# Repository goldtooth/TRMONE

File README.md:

View this project on [CADLAB.io](https://cadlab.io/project/1551). 

# TREMONE

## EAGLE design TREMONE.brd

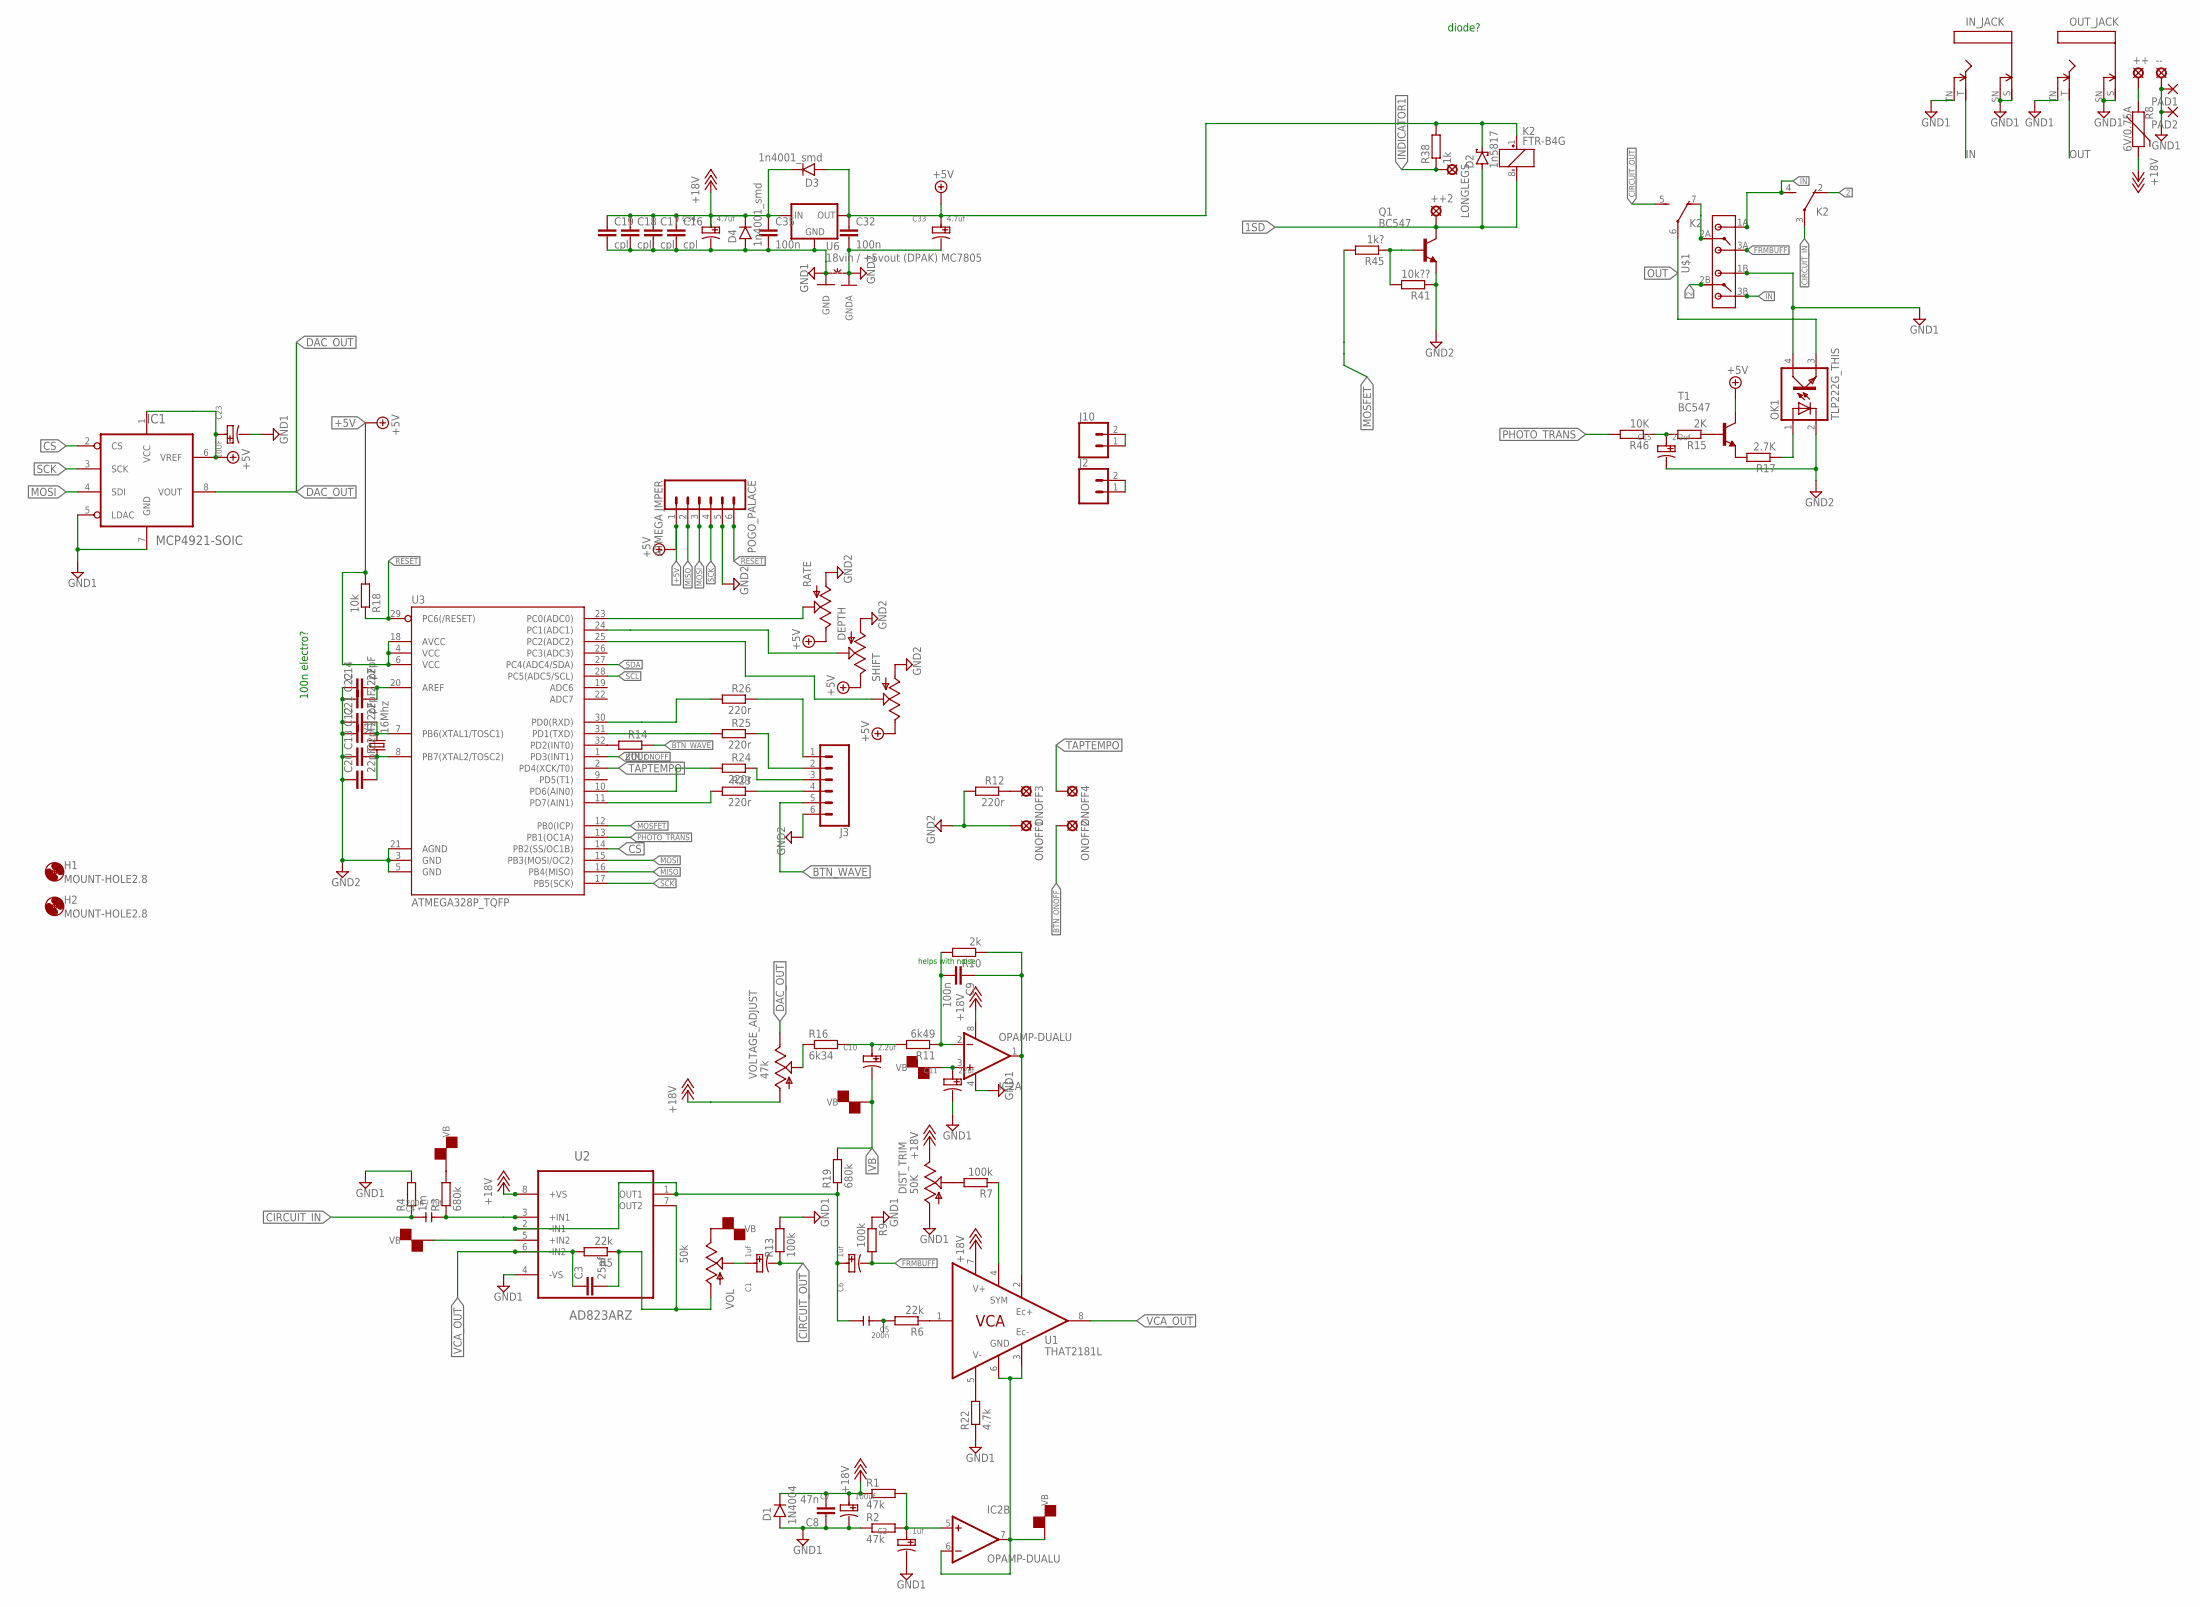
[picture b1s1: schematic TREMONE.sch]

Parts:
++, ++2: LSP10
--: LSP10
C1, C2, C6: 1uf; PC-D5.3MM
C3: 25pf; C1206
C4: 200n / 1uf; CERAMIC-5MM
C5: 200n; CERAMIC-5MM
C7: 100uf; PC-D5.3MM
C8: 47n; C1206
C9, C32, C35: 100n; C1206
C10, C15: 2.2uf; PC-D5.3MM
C11: 22uf; PC-D5.3MM
C12, C13, C22: 22pF; 0603
C14, C20, C21: 22pF; CAP-PTH-2.54
C16, C17, C18, C19: cpl; C1206
C23: 10UF; PC-D5.3MM
C33, C34: 4.7uf; PC-D5.3MM
D1: 1N4004; DO41-1
D2: 1n5817; SMB
D3, D4: 1n4001_smd; DO41-1
DEPTH: POT; ALPS_POT
DIST_TRIM: 50K; 3223G
H1, H2: MOUNT-HOLE2.8; 2,8
IC1: MCP4921-SOIC; SOIC-8
IC2: OPAMP-DUALU; SO08
IN_JACK: MMMONNNNOHOLES; MONONOHOLES
J2, J10: CONN_02PTH3; 1X02_LONGPADS
J3: CONN_06NO_SILK_FEMALE_PTH; 1X06_NO_SILK
K2: FTR-B4G
LONGLEGS: LSP10
OK1: TLP222G_THIS; DIL04
ONOFF1, ONOFF2, ONOFF3, ONOFF4: LSP10
OUT_JACK: MMMONNNNOHOLES; MONONOHOLES
PAD1, PAD2: SMD5; SMD2,54-5,08
POGO_PALACE: ATMEGA JMPER; 1X06_LONGPADS
Q1: BC547; TO92
R1, R2: 47k; M1206
R3, R19: 680k; M1206
R4: 1m; M1206
R5, R6: 22k; M1206
R7, R9, R13: 100k; M1206
R8: 6V/0.75A; 1206
R10: 2k; M1206
R11: 6k49; M1206
R12, R23, R24, R25, R26: 220r; M1206
R14: 200r; M1206
R15: 2K; M1206
R16: 6k34; M1206
R17: 2.7K; M1206
R18: 10k; M1206
R22: 4.7k; M1206
R38: 1k; M1206
R41: 10k??; M1206
R45: 1k?; M1206
R46: 10K; M1206
RATE: POT; ALPS_POT
SHIFT: POT; ALPS_POT
T1: BC547; TO92
U1: THAT2181L; SIP8
U2: AD823ARZ; SOIC127P600X175-8N
U3: ATMEGA328P_TQFP; TQFP32-08
U6: 18vin / +5vout (DPAK) MC7805; TO-252
U$1: BYSWITCH; BUFF/TRBYPASS
VOL: 50k; ALPS_POT
VOLTAGE_ADJUST: 47k; 3223G
Y1: 16Mhz; HC49US
~NUDEV~1: GND-GNDA1,27MM; GND-GNDA-1,27MM

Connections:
1SD: ++2.MP, D2.A, K2.8 (-), Q1.3 (C)
2: K2.2 (O), U$1.2B
+5V: C23.+, C32.1, C33.+, D2.C, D3.A, DEPTH.P$1 (E), IC1.1 (VCC), IC1.6 (VREF), K2.1 (+), POGO_PALACE.1, R18.2, R38.2, RATE.P$1 (E), SHIFT.P$1 (E), T1.3 (C), U3.4 (VCC), U3.6 (VCC), U3.18 (AVCC), U6.2 (OUT)
+18V: C7.+, C8.2, C16.1, C17.1, C18.1, C19.1, C34.+, C35.1, D1.C, D3.C, D4.C, DIST_TRIM.3 (E), IC2.8 (V+), R1.1, R8.2, U1.7 (V+), U2.8 (+VS), U6.1 (IN), VOLTAGE_ADJUST.1 (A)
BTN_ONOFF: ONOFF2.MP, U3.1 (PD3(INT1))
BTN_WAVE: J3.5, R14.1
CIRCUIT_IN: C4.1, K2.3, R4.1
CIRCUIT_OUT: C1.-, K2.5 (S), R13.1
CS: IC1.2 (CS), U3.14 (PB2(SS/OC1B))
DAC_OUT: IC1.8 (VOUT), VOLTAGE_ADJUST.3 (E)
FRMBUFF: C6.-, R9.2, U$1.3A
GND1: --.MP, C2.-, C7.-, C8.1, C11.-, C16.2, C17.2, C18.2, C19.2, C23.-, C34.-, C35.2, D1.A, D4.A, DIST_TRIM.1 (A), IC1.5 (LDAC), IC1.7 (GND), IC2.4 (V-), IN_JACK.S, IN_JACK.SN, IN_JACK.TN, OK1.4 (COL), OUT_JACK.S, OUT_JACK.SN, OUT_JACK.TN, PAD1.1, PAD2.1, R2.1, R4.2, R9.1, R13.2, R22.1, U2.4 (-VS), U6.3 (GND), U$1.1B, ~NUDEV~1.GND
GND2: C12.1, C13.1, C14.1, C15.-, C20.1, C21.1, C22.1, C32.2, C33.-, DEPTH.P$3 (A), J3.6, OK1.2 (C), ONOFF1.MP, POGO_PALACE.5, Q1.1 (E), R12.2, R41.1, RATE.P$3 (A), SHIFT.P$3 (A), U3.3 (GND), U3.5 (GND), U3.21 (AGND), ~NUDEV~1.GNDA
IN: IN_JACK.T, K2.4 (S), U$1.1A, U$1.3B
INDICATOR1: LONGLEGS.MP, R38.1
MISO: POGO_PALACE.2, U3.16 (PB4(MISO))
MOSFET: R45.2, U3.12 (PB0(ICP))
MOSI: IC1.4 (SDI), POGO_PALACE.3, U3.15 (PB3(MOSI/OC2))
unnamed: C4.2, R3.1, U2.3 (+IN1)
unnamed: C2.+, IC2.5 (+IN), R1.2, R2.2
unnamed: ONOFF3.MP, R12.1
unnamed: R16.1, VOLTAGE_ADJUST.2 (S)
unnamed: C3.2, R5.1, U2.7 (OUT2), VOL.P$3 (A)
unnamed: C5.2, C6.+, R19.1, U2.1 (OUT1), U2.2 (-IN1)
unnamed: C5.1, R6.2
unnamed: R6.1, U1.1 (IN)
unnamed: C1.+, VOL.P$2 (S)
unnamed: J2.1, J2.2
unnamed: R7.1, U1.4 (SYM)
unnamed: DIST_TRIM.2 (S), R7.2
unnamed: C13.2, C20.2, U3.8 (PB7(XTAL2/TOSC2)), Y1.1
unnamed: C9.2, IC2.2 (-IN), R10.2, R11.1
unnamed: C12.2, C21.2, U3.7 (PB6(XTAL1/TOSC1)), Y1.2
unnamed: C14.2, C22.2, U3.20 (AREF)
unnamed: J3.4, R23.1
unnamed: J3.3, R24.1
unnamed: J3.2, R25.1
unnamed: J10.1, J10.2
unnamed: R22.2, U1.5 (V-)
unnamed: J3.1, R26.1
unnamed: R26.2, U3.30 (PD0(RXD))
unnamed: R25.2, U3.31 (PD1(TXD))
unnamed: R24.2, U3.10 (PD6(AIN0))
unnamed: R23.2, U3.11 (PD7(AIN1))
unnamed: RATE.P$2 (S), U3.23 (PC0(ADC0))
unnamed: DEPTH.P$2 (S), U3.24 (PC1(ADC1))
unnamed: SHIFT.P$2 (S), U3.25 (PC2(ADC2))
unnamed: R14.2, U3.32 (PD2(INT0))
unnamed: C15.+, R15.2, R46.1
unnamed: R15.1, T1.2 (B)
unnamed: ++.MP, R8.1
unnamed: C9.1, IC2.1 (OUT), R10.1, U1.2 (EC+)
unnamed: R17.2, T1.1 (E)
unnamed: OK1.1 (A), R17.1
unnamed: K2.7 (O), U$1.2A
unnamed: Q1.2 (B), R41.2, R45.1
OUT: K2.6, OK1.3 (EMIT), OUT_JACK.T
PHOTO_TRANS: R46.2, U3.13 (PB1(OC1A))
R: C10.+, R11.2, R16.2
RESET: POGO_PALACE.6, R18.1, U3.29 (PC6(/RESET))
SCK: IC1.3 (SCK), POGO_PALACE.4, U3.17 (PB5(SCK))
SCL: U3.28 (PC5(ADC5/SCL))
SDA: U3.27 (PC4(ADC4/SDA))
TAPTEMPO: ONOFF4.MP, U3.2 (PD4(XCK/T0))
VB: C10.-, C11.+, IC2.3 (+IN), IC2.6 (-IN), IC2.7 (OUT), R3.2, R19.2, U1.3 (EC-), U1.6 (GND), U2.5 (+IN2), VOL.P$1 (E)
VCA_OUT: C3.1, R5.2, U1.8 (OUT), U2.6 (-IN2)

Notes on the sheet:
100n electro?
helps with noise
diode?

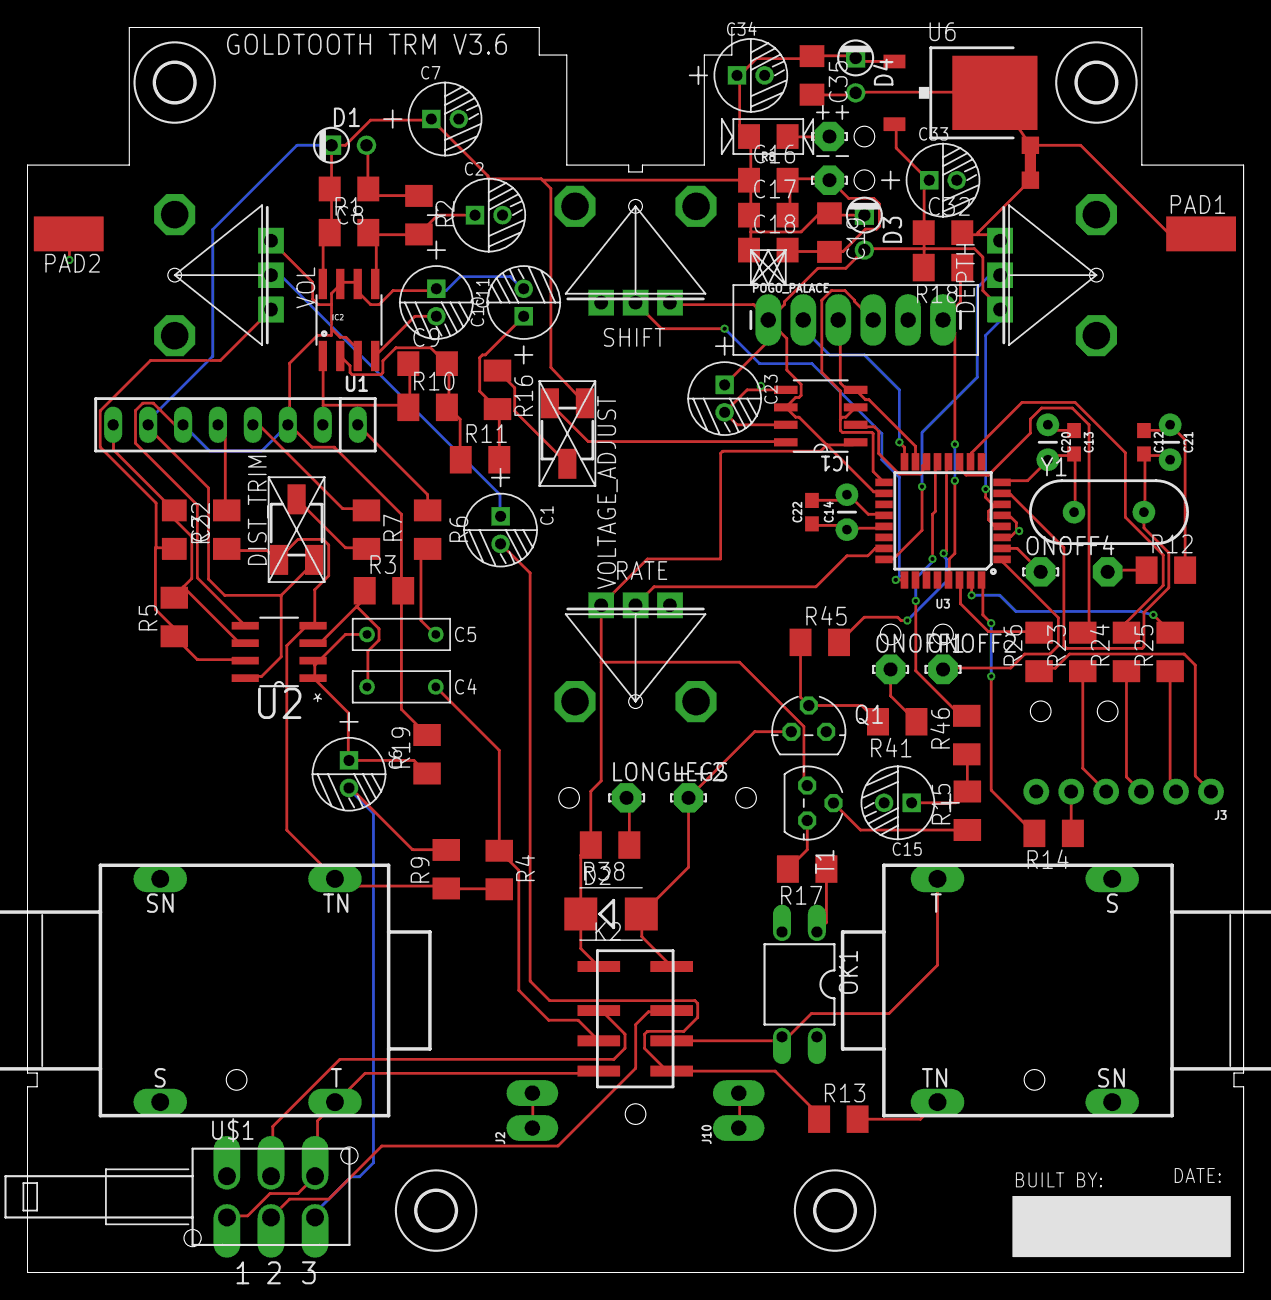
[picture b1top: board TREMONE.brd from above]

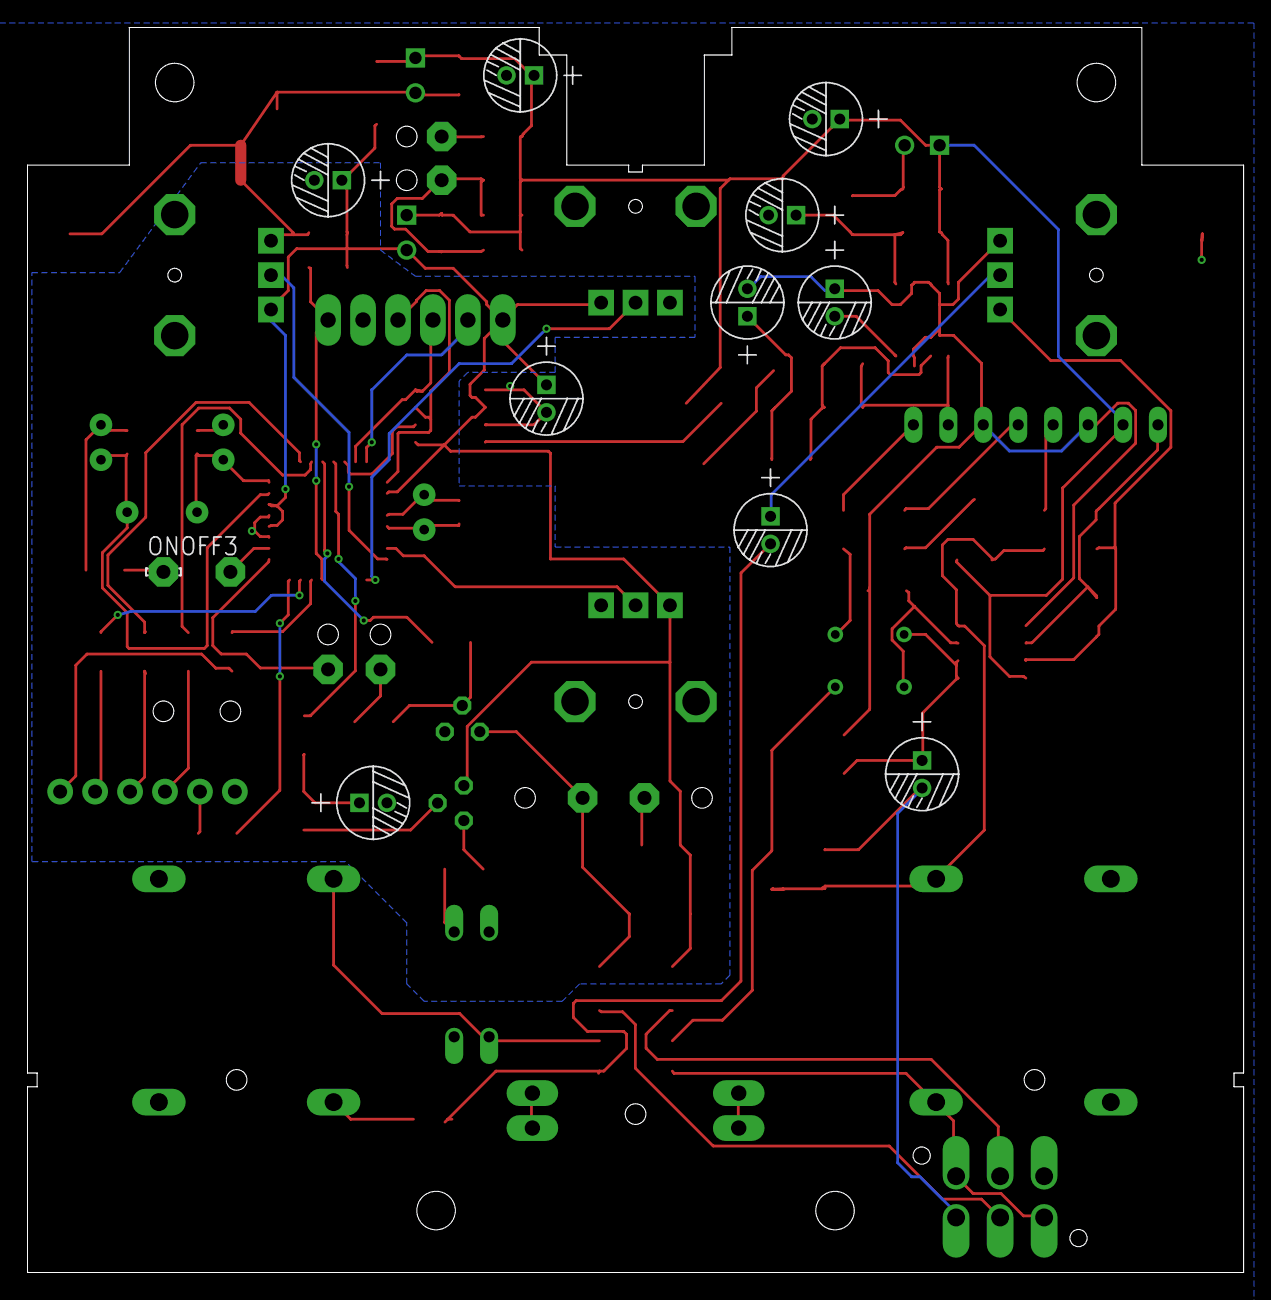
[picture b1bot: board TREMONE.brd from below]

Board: 2 copper layers, 88.4 x 90.5 mm, 109 parts (5 on the bottom side), 64 nets.

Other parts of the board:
H3, H4: MOUNT-HOLE2.8; 2,8
U$2, U$3, U$5, U$9, U$11, U$12, U$13, U$14, U$15, U$20, U$22: HOLD

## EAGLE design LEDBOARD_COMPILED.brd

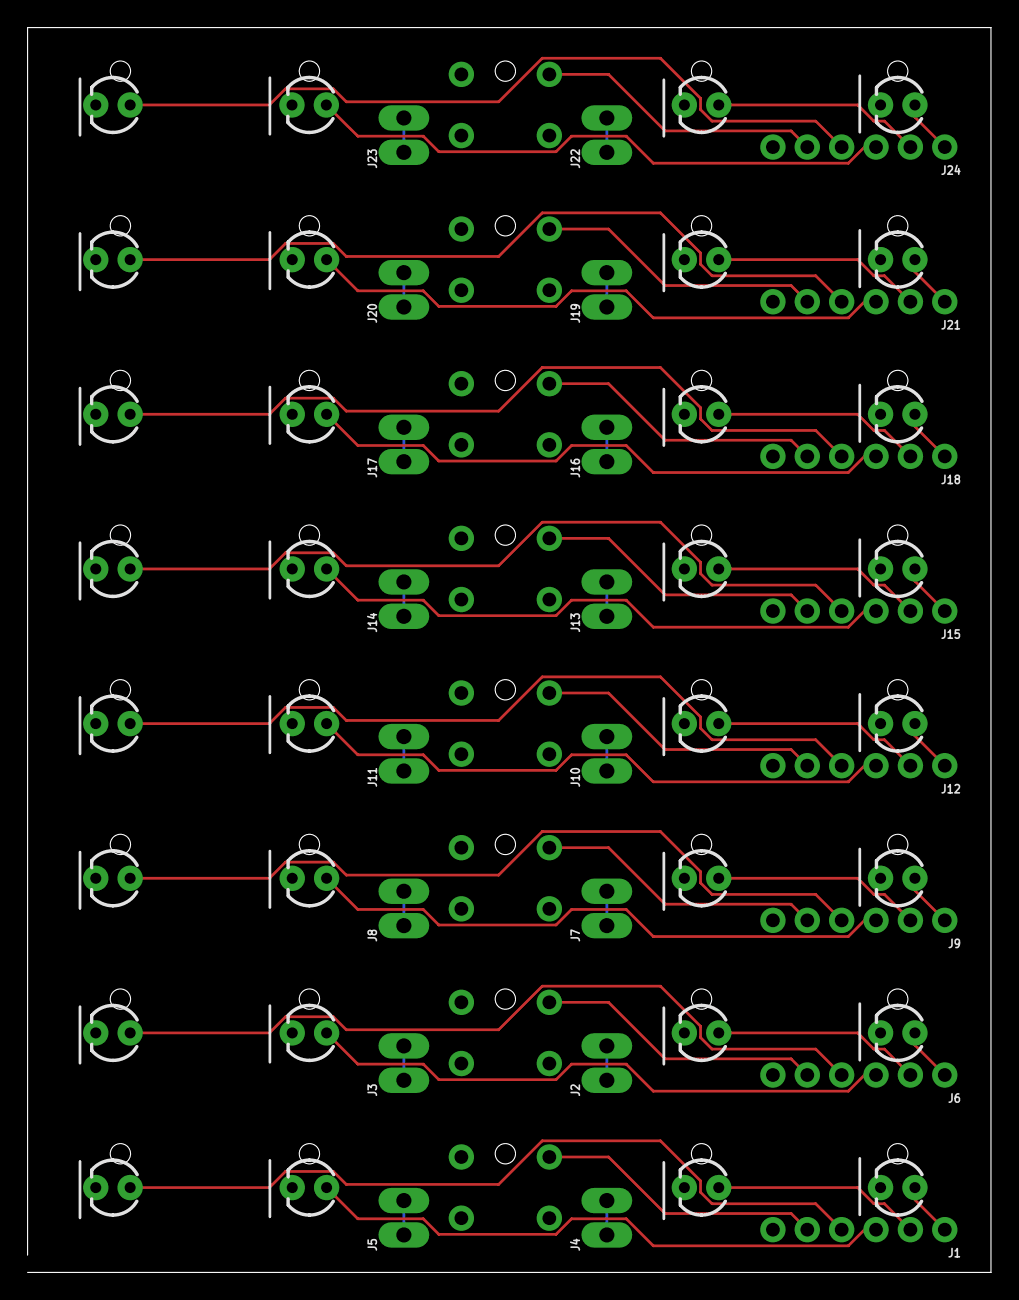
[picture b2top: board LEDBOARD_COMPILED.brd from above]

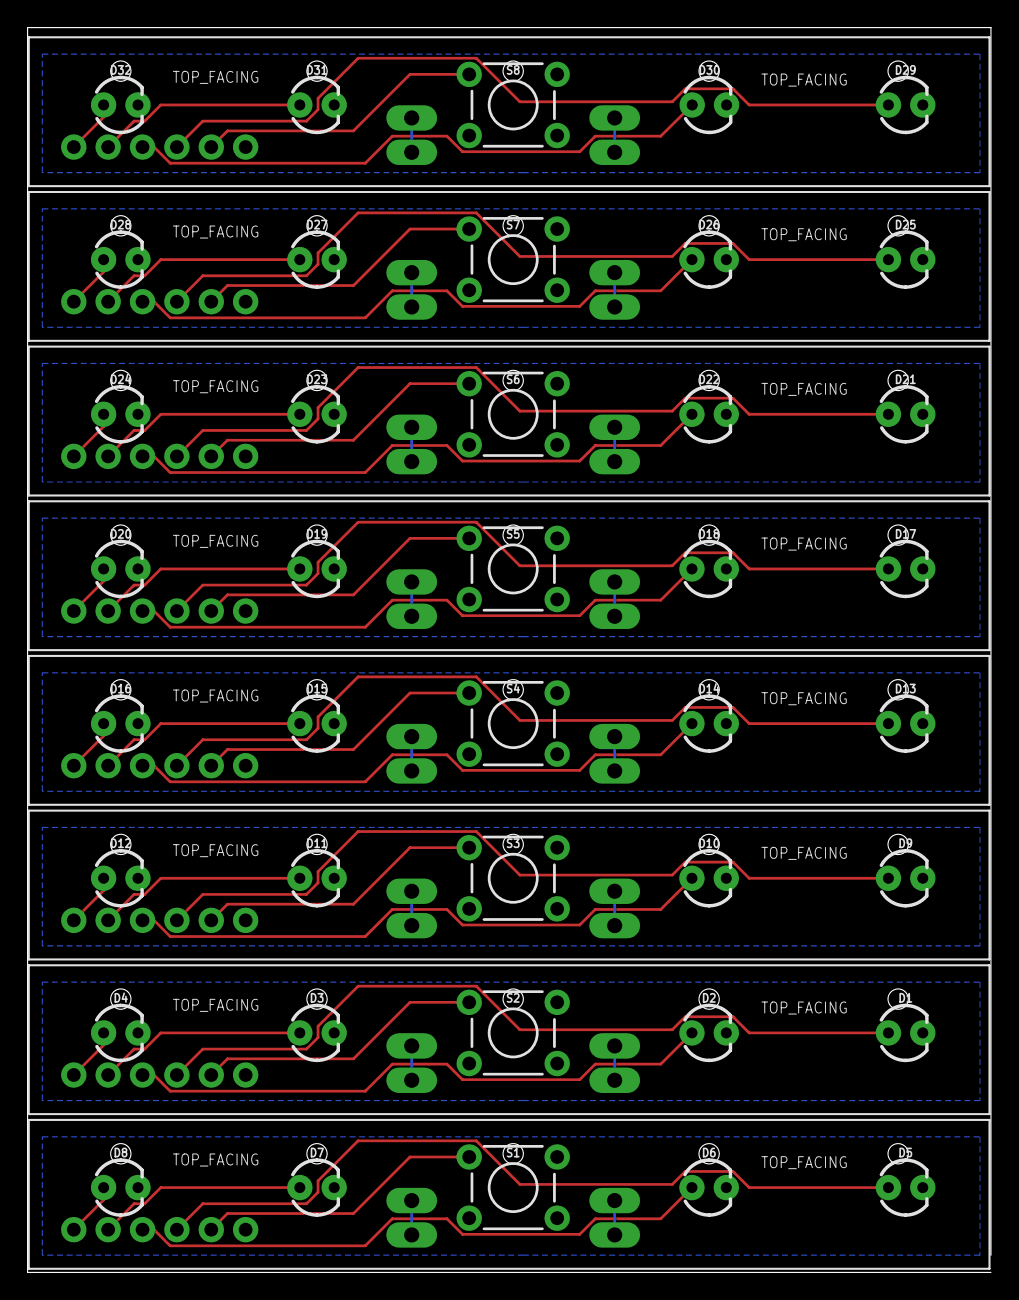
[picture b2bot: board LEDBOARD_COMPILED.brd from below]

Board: 2 copper layers, 71.2 x 92.0 mm, 104 parts (40 on the bottom side), 64 nets.

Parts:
D1, D2, D3, D4, D5, D6, D7, D8, D9, D10, D11, D12, D13, D14, D15, D16, D17, D18, D19, D20, D21, D22, D23, D24, D25, D26, D27, D28, D29, D30, D31, D32: LED_3MM
J1, J6, J9, J12, J15, J18, J21, J24: 1X06_NO_SILK
J2, J3, J4, J5, J7, J8, J10, J11, J13, J14, J16, J17, J19, J20, J22, J23: 1X02_LONGPADS
S1, S2, S3, S4, S5, S6, S7, S8: MOMENTARY-SWITCH-SPST-PTH-6.0MM; TACTILE_SWITCH_PTH_6.0MM
U$1, U$2, U$3, U$4, U$5, U$6, U$7, U$8, U$9, U$10, U$11, U$12, U$13, U$14, U$15, U$16, U$17, U$18, U$19, U$20, U$21, U$22, U$23, U$24, U$25, U$26, U$27, U$28, U$29, U$30, U$31, U$32, U$33, U$34, U$35, U$36, U$37, U$38, U$39, U$40: HOLD

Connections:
unnamed: D4.A, J6.1
unnamed: D3.A, J6.2
unnamed: D2.A, J6.3
unnamed: D1.A, J6.4
unnamed: D1.K, D2.K, D3.K, D4.K, J6.6, S2.3
unnamed: J2.1, J2.2
unnamed: J3.1, J3.2
unnamed: J6.5, S2.1
unnamed: D12.A, J9.1
unnamed: D11.A, J9.2
unnamed: D10.A, J9.3
unnamed: D9.A, J9.4
unnamed: D9.K, D10.K, D11.K, D12.K, J9.6, S3.3
unnamed: J7.1, J7.2
unnamed: J8.1, J8.2
unnamed: J9.5, S3.1
unnamed: D16.A, J12.1
unnamed: D15.A, J12.2
unnamed: D14.A, J12.3
unnamed: D13.A, J12.4
unnamed: D13.K, D14.K, D15.K, D16.K, J12.6, S4.3
unnamed: J10.1, J10.2
unnamed: J11.1, J11.2
unnamed: J12.5, S4.1
unnamed: D20.A, J15.1
unnamed: D19.A, J15.2
unnamed: D18.A, J15.3
unnamed: D17.A, J15.4
unnamed: D17.K, D18.K, D19.K, D20.K, J15.6, S5.3
unnamed: J13.1, J13.2
unnamed: D5.K, D6.K, D7.K, D8.K, J1.6, S1.3
unnamed: D8.A, J1.1
unnamed: D7.A, J1.2
unnamed: D6.A, J1.3
unnamed: D5.A, J1.4
unnamed: J1.5, S1.1
unnamed: J4.1, J4.2
unnamed: J5.1, J5.2
unnamed: J14.1, J14.2
unnamed: J15.5, S5.1
unnamed: D24.A, J18.1
unnamed: D23.A, J18.2
unnamed: D22.A, J18.3
unnamed: D21.A, J18.4
unnamed: D21.K, D22.K, D23.K, D24.K, J18.6, S6.3
unnamed: J16.1, J16.2
unnamed: J17.1, J17.2
unnamed: J18.5, S6.1
unnamed: D28.A, J21.1
unnamed: D27.A, J21.2
unnamed: D26.A, J21.3
unnamed: D25.A, J21.4
unnamed: D25.K, D26.K, D27.K, D28.K, J21.6, S7.3
unnamed: J19.1, J19.2
unnamed: J20.1, J20.2
unnamed: J21.5, S7.1
unnamed: D32.A, J24.1
unnamed: D31.A, J24.2
unnamed: D30.A, J24.3
unnamed: D29.A, J24.4
unnamed: D29.K, D30.K, D31.K, D32.K, J24.6, S8.3
unnamed: J22.1, J22.2
unnamed: J23.1, J23.2
unnamed: J24.5, S8.1

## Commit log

2019-01-07 Removed gerbers
    Removed Gerbers
2019-01-07 Backlink to CADLAB.io has been added.
2019-01-20 v3.3
2019-01-21 connectors for jackbaord
2019-03-11 move jacks in
2019-03-12 ordered 120119
2019-05-07 dunno
2019-06-23 silent switch

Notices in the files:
parts and their libraries:
SparkFun-Connectors: Licensing: Creative Commons ShareAlike 4.0 International - https://creativecommons.org/licenses/by-sa/4.0
that-corp: Copyright (C) 2008-2010, Bob Starr
